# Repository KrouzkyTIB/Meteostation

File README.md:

# Meteostanice

Toto je projekt kroužku bastlení s rodiči z letního pololetí roku 2023. 

## Módy
Meteostanice je možné používat ve dvou módech. Podle toho zdali je připojena v lokální síti či nikoliv. Módy se liší pouze v tom, že pokud máte stanici připojenou k Wi-Fi, tak je možné se na ní připojit pomocí Vašeho telefonu či jiného zařízení a nechat si zobrazit teplotu a vlhkost ve webové stránce. V obou případech funguje display stejně, takže pokud se nechcete koukat přes webový prohlížeč na naměřené teploty, tak není potřeba si s tímto krokem lámat hlavu.
### Stanice není připojená k Wi-Fi
Stanici v tomto módu čeká, až se bude moci připojit na lokální Wi-Fi. Pro to aby to mohla udělat je nutné, jí předat ssid (jméno) a heslo k Vaší domácí Wi-Fi. Pro tento účel meteostanice vytvoří přístupový bod jehož jméno se objeví na horním řádku displaye.
Po připojení na přístupový bod je potřeba zadat do prohlížeče kam zadáváte doménu zadat IP adresu napsanou na displayi na druhém řádku. V tomto případě je IP adresa nastavena na 192.168.0.10. Po zadání adresy do prohlížeče by se Vám měla zobrazit webová stránka na které je možné vyplnit jméno a heslo lokální Wi-Fi sítě.
Do webové stránky zadejte Vaše přístupové údaje a potvrďte, poté začne blikat LED dioda na stanici označující, že se stanice snaží připojit na lokální síť. Poté až blikání ustane tak je Vaše stanice úspěšně připojena k lokální síti. 
Pokud blikání do cca půl minuty nepřestane tak je velice pravděpodobné, že jste udělali někde chybu při zadávání přihlašovacích údajů do stanice a stanice se nemůže připojit. Pokud se Vám toto stane tak je potřeba kkliknout na tlačítko RST_WIFI, ktera vymaže Wi-Fi nastavení a následně je potřeba restartovat zařízení pomocí tlačítka RST nebo zapnutím a vypnutím. Tím uvedete stanici do továrního nastavení a můžete to zkusit znovu.
Po zadání přihlašovacích údajů k Wi-Fi síti si je meteostanice sama uloží do paměti a bude se poté vždy automaticky připojovat.
### Stanice je připojena k Wi-Fi
V tomto módu máte Vaši stanici připojenou k Wi-Fi síti. Meteostanice Vám po svém zapnutí na display vypíše, že je připojena a napíše Vám IP adresu, kterou dostala přiřazenou od Vaše routeru (přístupového bodu). Tuto adresu je dobré si poznamenat, protože při každém restartu může meteostanice dostat jinou IP adresu pod kterou se na ni můžete připojit.
Po zadání IP adresy zařízení do prohlížeče Vaše telefonu či jiného zařízení se Vám objeví stránka s aktuálními naměřenými hodnotami a s možností vymazat přihlašovací údaje k lokální síti a tím opět uvést zařízení do předchozího módu.

#### Poznámka na závěr
Je důležité brát v potaz to, že se jedná o poměrně slabý čip a může se tak stát to, že bude prodleva načítání stránek trošku delší než jste zvyklí u běžných webových stránek. Ze stejného důvodu je omezen maximální počet připojených zařízení v prvním módu na 1 zařízení.

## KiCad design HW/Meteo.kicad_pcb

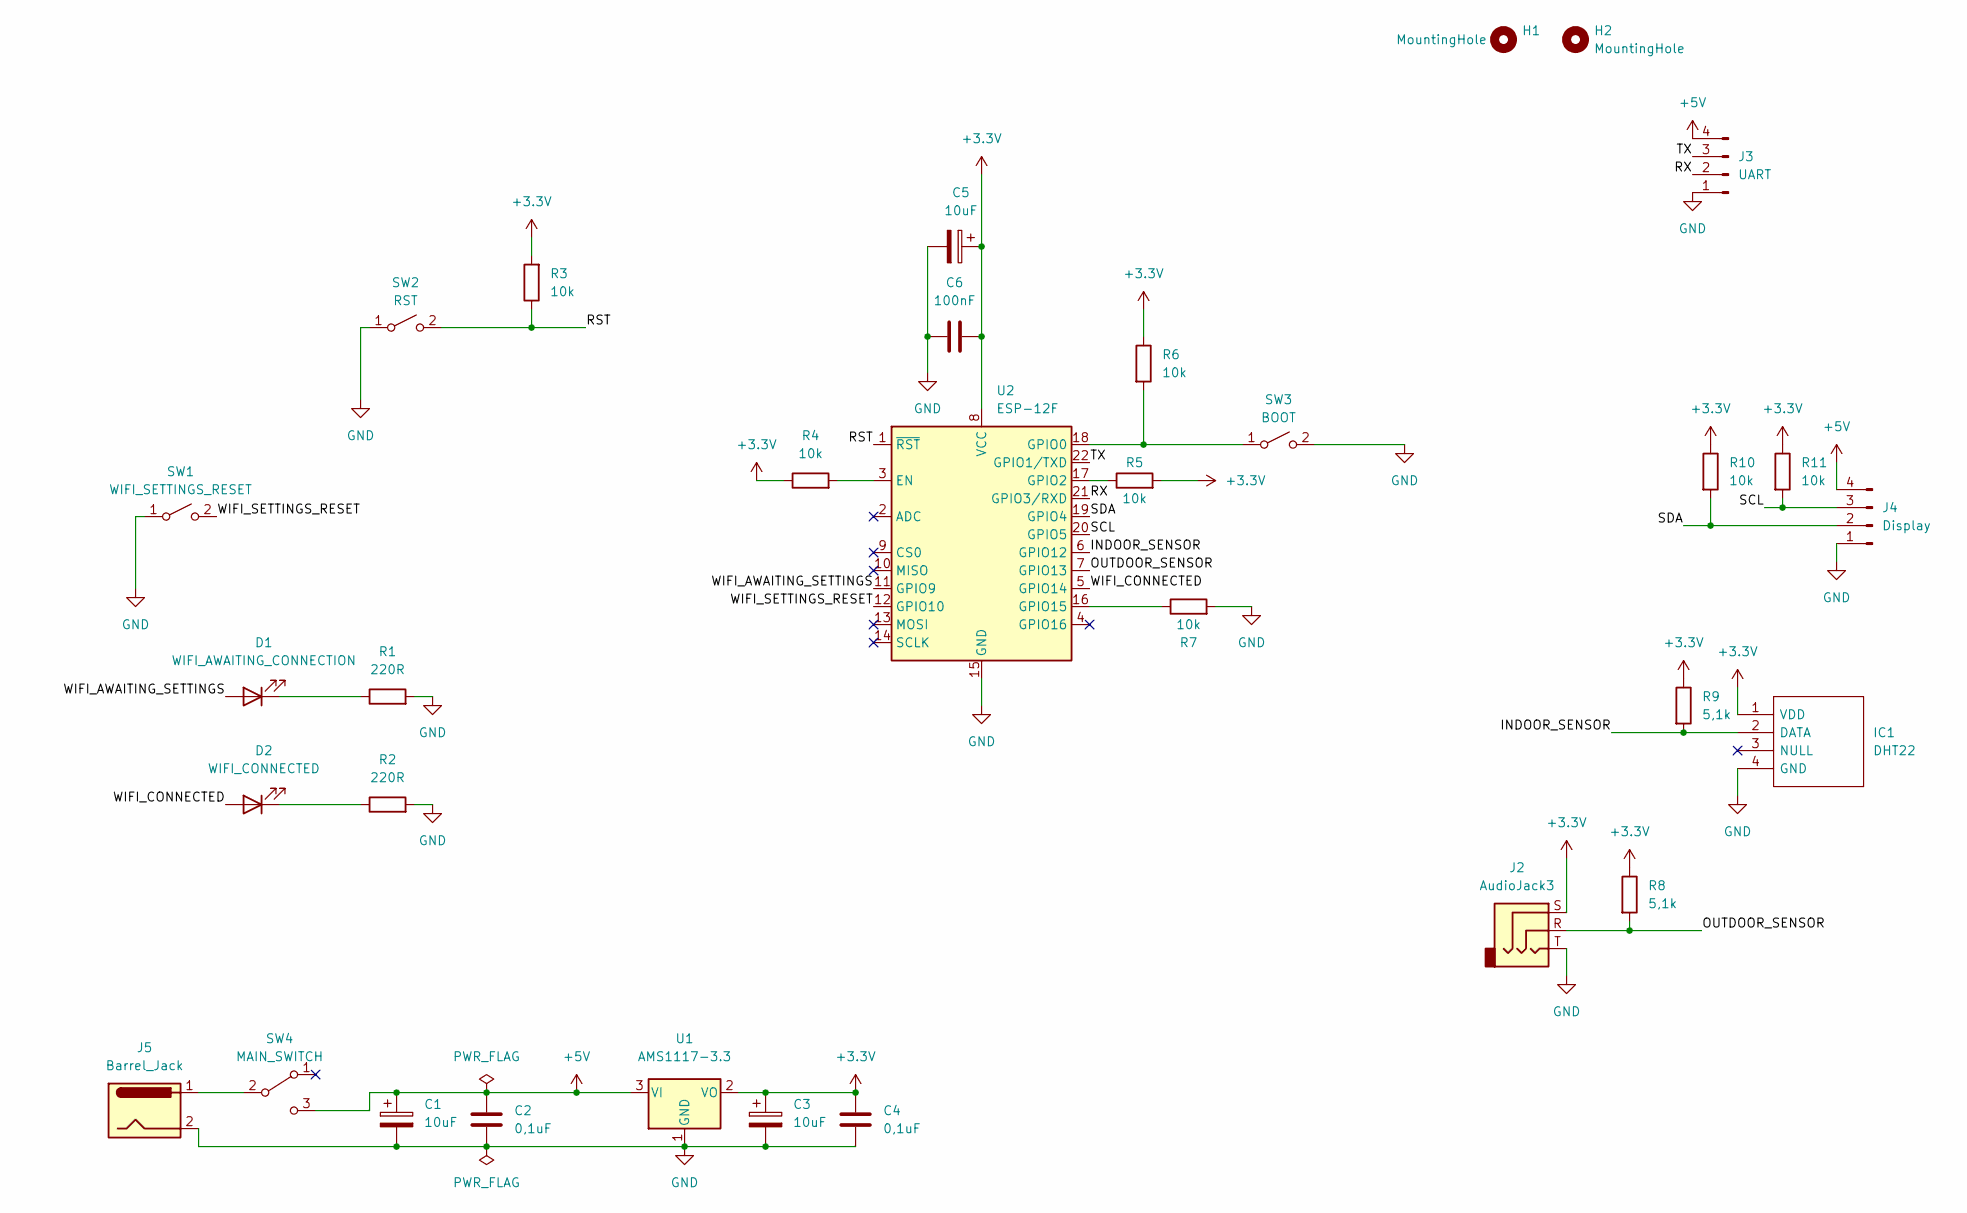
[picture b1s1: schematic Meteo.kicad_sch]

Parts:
C1, C3, C5: 10uF; CP_Radial_D5.0mm_P2.50mm
C2, C4: 0,1uF; C_Disc_D3.0mm_W1.6mm_P2.50mm
C6: 100nF; C_Disc_D3.0mm_W1.6mm_P2.50mm
D1: WIFI_AWAITING_CONNECTION; LED_D3.0mm
D2: WIFI_CONNECTED; LED_D3.0mm
H1, H2: MountingHole; MountingHole_3.2mm_M3
IC1: DHT22; Manufacturer_Part_Number DHT22
J2: AudioJack3; Jack_3.5mm_CUI_SJ1-3525N_Horizontal
J3: UART; PinHeader_1x04_P2.54mm_Vertical
J4: Display; PinHeader_1x04_P2.54mm_Vertical
J5: Barrel_Jack; BarrelJack_Horizontal
R1, R2: 220R; R_Axial_DIN0207_L6.3mm_D2.5mm_P7.62mm_Horizontal
R3, R4, R5, R6, R7, R10, R11: 10k; R_Axial_DIN0207_L6.3mm_D2.5mm_P7.62mm_Horizontal
R8, R9: 5,1k; R_Axial_DIN0207_L6.3mm_D2.5mm_P7.62mm_Horizontal
SW1: WIFI_SETTINGS_RESET; SW_PUSH_6mm
SW2: RST; SW_PUSH_6mm
SW3: BOOT; SW_PUSH_6mm
SW4: MAIN_SWITCH; SW_CuK_OS102011MA1QN1_SPDT_Angled
U1: AMS1117-3.3; SOT-223-3_TabPin2
U2: ESP-12F; ESP-12E

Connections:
+3.3V: C3.1, C4.1, C5.1, C6.2, IC1.1 (VDD), J2.S, R3.2, R4.1, R5.2, R6.1, R8.1, R9.1, R10.1, R11.1, U1.2 (VO), U2.8 (VCC)
+5V: C1.1, C2.1, J3.4, J4.4, SW4.3 (C), U1.3 (VI)
/INDOOR_SENSOR: IC1.2 (DATA), R9.2, U2.6 (GPIO12)
/OUTDOOR_SENSOR: J2.R, R8.2, U2.7 (GPIO13)
/RST: R3.1, SW2.2 (B), U2.1 (~RST)
/RX: J3.2, U2.21 (GPIO3/RXD)
/SCL: J4.3, R11.2, U2.20 (GPIO5)
/SDA: J4.2, R10.2, U2.19 (GPIO4)
/TX: J3.3, U2.22 (GPIO1/TXD)
/WIFI_AWAITING_SETTINGS: D1.2 (A), U2.11 (GPIO9)
/WIFI_CONNECTED: D2.2 (A), U2.5 (GPIO14)
/WIFI_SETTINGS_RESET: SW1.2 (B), U2.12 (GPIO10)
GND: C1.2, C2.2, C3.2, C4.2, C5.2, C6.1, IC1.4 (GND), J2.T, J3.1, J4.1, J5.2, R1.2, R2.2, R7.2, SW1.1 (A), SW2.1 (A), SW3.2 (B), U1.1 (GND), U2.15 (GND)
unnamed: D1.1 (K), R1.1
unnamed: D2.1 (K), R2.1
unnamed: J5.1, SW4.2 (B)
unnamed: R4.2, U2.3 (EN)
unnamed: R5.1, U2.17 (GPIO2)
unnamed: R6.2, SW3.1 (A), U2.18 (GPIO0)
unnamed: R7.1, U2.16 (GPIO15)

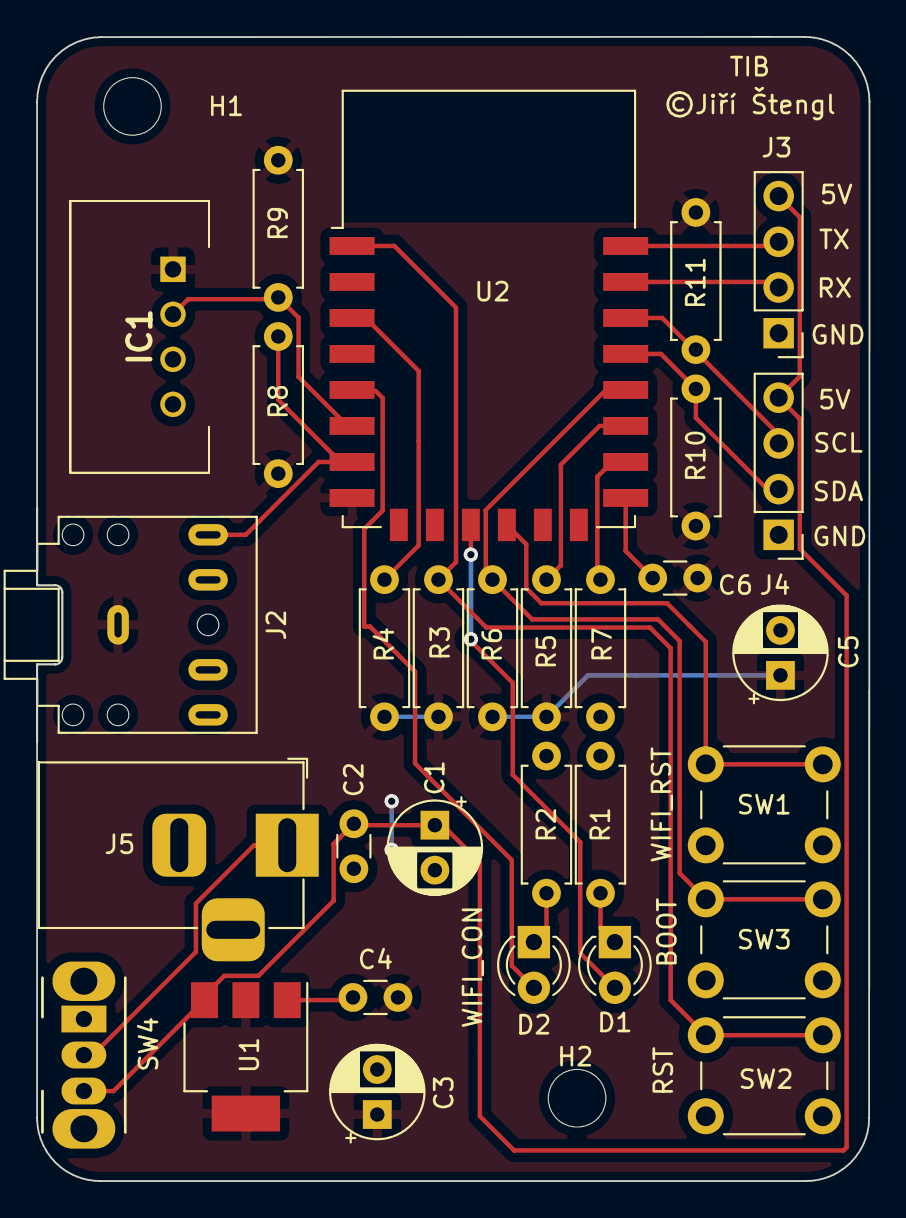
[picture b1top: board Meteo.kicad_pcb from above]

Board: 2 copper layers, 46.2 x 63.5 mm, 32 parts (0 on the bottom side), 20 nets.

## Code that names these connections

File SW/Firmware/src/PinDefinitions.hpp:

//
// Created by jiri on 1.3.23.
//

#ifndef FIRMWARE_PINDEFINITIONS_HPP
#define FIRMWARE_PINDEFINITIONS_HPP

#define TEST_LED_PIN 9
#define RESET_WIFI_SETTINGS_PIN 10
#define INDOOR_SENSOR_PIN 12
#define OUTDOOR_SENSOR_PIN 13
#define WIFI_CONNECTED_PIN 14
#endif //FIRMWARE_PINDEFINITIONS_HPP

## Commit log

2023-02-28 Hardware status + gitignore
2023-03-01 Initial sowftware commit
2023-03-01 Running indoor temperature sensor
2023-03-01 Display API done
2023-03-01 Display auto update
2023-03-01 Working outdoor sensor
2023-03-04 Prepared frontend for ESP
2023-03-04 Prepared wrapper for file system
2023-03-04 Prepared wifi handler init
2023-03-04 Working stationary wifi endpoint
2023-03-04 Working web server
2023-03-04 Working web page with value
2023-03-05 Done wifi config page
2023-03-05 Serving wifi config page done
2023-03-05 Working setting of WiFi
2023-03-05 Working connecting to WiFi
2023-03-05 Upgraded connected texts
2023-03-05 Fixed styling
2023-03-05 Turning backlight on/off done
2023-03-05 Working reset wifi endpoint
2023-03-05 Working reset wifi by button

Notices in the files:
HW/Meteo.kicad_pcb:
©Jiří Štengl
